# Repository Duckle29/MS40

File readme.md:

View this project on [CADLAB.io](https://cadlab.io/project/2268). 

# MS40

[Interactive BOM](https://duckle29.github.io/MS40/ibom.html)

The project uses Ai03s keyswitch library.
Many thanks to Ai03 for releasing an awesome keyswitch library with an entirely open license.

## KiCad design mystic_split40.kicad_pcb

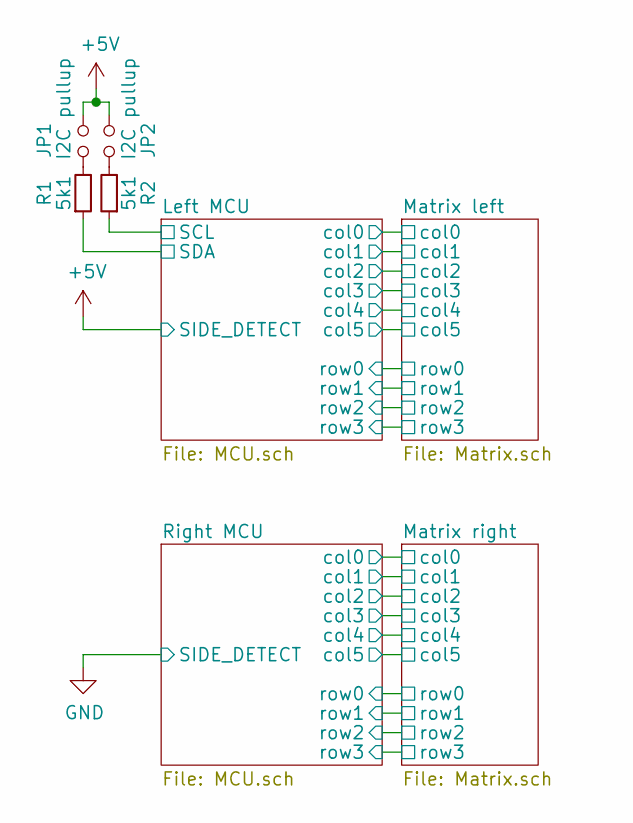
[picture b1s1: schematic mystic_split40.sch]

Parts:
JP1, JP2: I2C pullup; SolderJumper-2_P1.3mm_Open_TrianglePad1.0x1.5mm
R1, R2: 5k1; R_0603_1608Metric_Pad1.05x0.95mm_HandSolder

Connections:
+5V: JP1.1, JP2.1; also elsewhere on the board
/Left MCU/SCL: R2.1; also elsewhere on the board
/Left MCU/SDA: R1.1; also elsewhere on the board
unnamed: JP1.2, R1.2
unnamed: JP2.2, R2.2

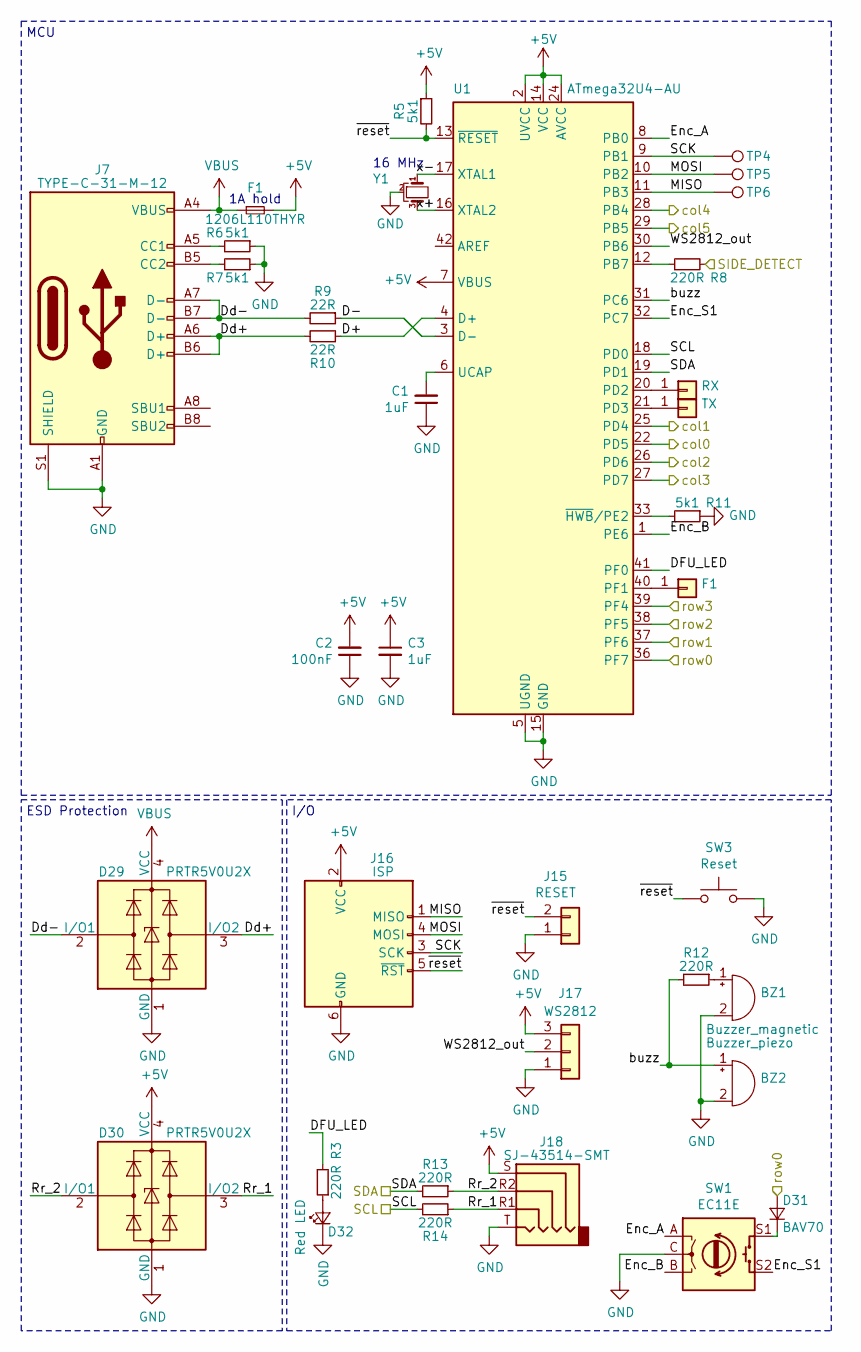
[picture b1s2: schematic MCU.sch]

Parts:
BZ1: Buzzer_magnetic; Buzzer_12x9.5RM7.6
BZ2: Buzzer_piezo; Buzzer_Mallory_AST1109MLTRQ
C1, C3: 1uF; C_0603_1608Metric_Pad1.05x0.95mm_HandSolder
C2: 100nF; C_0603_1608Metric_Pad1.05x0.95mm_HandSolder
D29, D30: PRTR5V0U2X; SOT-143
D31: BAV70; D_SOD-323_HandSoldering
D32: Red LED; LED_0805_2012Metric_Pad1.15x1.40mm_HandSolder
F1: 1206L110THYR; Fuse_1206_3216Metric_Pad1.42x1.75mm_HandSolder
J1: RX; TestPoint_Pad_D1.0mm
J2: TX; TestPoint_Pad_D1.0mm
J6: F1; TestPoint_Pad_D1.0mm
J7: TYPE-C-31-M-12; USB_C_Receptacle_HRO_TYPE-C-31-M-12
J15: RESET; PinHeader_1x02_P2.54mm_Vertical
J16: ISP; Tag-Connect_TC2030-IDC-NL_2x03_P1.27mm_Vertical
J17: WS2812; PinHeader_1x03_P2.54mm_Vertical
J18: SJ-43514-SMT
R3, R8, R12, R13, R14: 220R; R_0603_1608Metric_Pad1.05x0.95mm_HandSolder
R5, R6, R7, R11: 5k1; R_0603_1608Metric_Pad1.05x0.95mm_HandSolder
R9, R10: 22R; R_0603_1608Metric_Pad1.05x0.95mm_HandSolder
SW1: EC11E; RotaryEncoder_Alps_EC11E-Switch_Vertical_H20mm
SW3: Reset; SW_SPST_CK_RS282G05A3
TP4: SCK; TestPoint_Pad_D1.0mm
TP5: MOSI; TestPoint_Pad_D1.0mm
TP6: MISO; TestPoint_Pad_D1.0mm
U1: ATmega32U4-AU; TQFP-44_10x10mm_P0.8mm
Y1: CSTNE16M0VH3L000R0; Resonator_SMD_muRata_CSTxExxV-3Pin_3.0x1.1mm_HandSoldering

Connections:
+5V: C2.2, C3.1, D30.4 (VCC), F1.2, J16.2 (VCC), J17.3, J18.S, R5.1, R8.2, U1.2 (UVCC), U1.7 (VBUS), U1.14 (VCC), U1.24 (AVCC), U1.34 (VCC), U1.44 (AVCC); also elsewhere on the board
/Left MCU/D+: R10.1, U1.4 (D+)
/Left MCU/D-: R9.1, U1.3 (D-)
/Left MCU/DFU_LED: R3.2, U1.41 (PF0)
/Left MCU/Dd+: D29.3 (I/O2), J7.A6 (D+), J7.B6 (D+), R10.2
/Left MCU/Dd-: D29.2 (I/O1), J7.A7 (D-), J7.B7 (D-), R9.2
/Left MCU/Enc_A: SW1.A, U1.8 (PB0)
/Left MCU/Enc_B: SW1.B, U1.1 (PE6)
/Left MCU/Enc_S1: SW1.S2, U1.32 (PC7)
/Left MCU/MISO: J16.1 (MISO), TP6.1, U1.11 (PB3)
/Left MCU/MOSI: J16.4 (MOSI), TP5.1, U1.10 (PB2)
/Left MCU/Rr_1: D30.3 (I/O2), J18.R1, R14.1
/Left MCU/Rr_2: D30.2 (I/O1), J18.R2, R13.1
/Left MCU/SCK: J16.3 (SCK), TP4.1, U1.9 (PB1)
/Left MCU/SCL: R14.2, U1.18 (PD0); also elsewhere on the board
/Left MCU/SDA: R13.2, U1.19 (PD1); also elsewhere on the board
/Left MCU/WS2812_out: J17.2, U1.30 (PB6)
/Left MCU/buzz: BZ2.1 (-), R12.2, U1.31 (PC6)
/Left MCU/col0: U1.22 (PD5); also elsewhere on the board
/Left MCU/col1: U1.25 (PD4); also elsewhere on the board
/Left MCU/col2: U1.26 (PD6); also elsewhere on the board
/Left MCU/col3: U1.27 (PD7); also elsewhere on the board
/Left MCU/col4: U1.28 (PB4); also elsewhere on the board
/Left MCU/col5: U1.29 (PB5); also elsewhere on the board
/Left MCU/row0: D31.2 (A), U1.36 (PF7); also elsewhere on the board
/Left MCU/row1: U1.37 (PF6); also elsewhere on the board
/Left MCU/row2: U1.38 (PF5); also elsewhere on the board
/Left MCU/row3: U1.39 (PF4); also elsewhere on the board
/Left MCU/x+: U1.16 (XTAL2), Y1.3
/Left MCU/x-: U1.17 (XTAL1), Y1.1
/Left MCU/~reset: J15.2, J16.5 (~RST), R5.2, SW3.1, U1.13 (~RESET)
GND: BZ1.2 (+), BZ2.2 (+), C1.1, C2.1, C3.2, D29.1 (GND), D30.1 (GND), D32.1 (K), J7.A1 (GND), J7.A12 (GND), J7.B1 (GND), J7.B12 (GND), J7.S1 (SHIELD), J15.1, J16.6 (GND), J17.1, J18.T, R6.1, R7.1, R11.1, SW1.C, SW1.MP, SW3.2, U1.5 (UGND), U1.15 (GND), U1.23 (GND), U1.35 (GND), U1.43 (GND), Y1.2; also elsewhere on the board
unnamed: BZ1.1 (-), R12.1
unnamed: C1.2, U1.6 (UCAP)
unnamed: D31.1 (K), SW1.S1
unnamed: D32.2 (A), R3.1
unnamed: J1.1, U1.20 (PD2)
unnamed: J2.1, U1.21 (PD3)
unnamed: J6.1, U1.40 (PF1)
unnamed: J7.A5 (CC1), R6.2
unnamed: J7.B5 (CC2), R7.2
unnamed: R8.1, U1.12 (PB7)
unnamed: R11.2, U1.33 (~HWB~/PE2)
VBUS: D29.4 (VCC), F1.1, J7.A4 (VBUS), J7.A9 (VBUS), J7.B4 (VBUS), J7.B9 (VBUS); also elsewhere on the board

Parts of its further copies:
BZ3: Buzzer_magnetic; Buzzer_12x9.5RM7.6
BZ4: Buzzer_piezo; Buzzer_Mallory_AST1109MLTRQ
C4, C6: 1uF; C_0603_1608Metric_Pad1.05x0.95mm_HandSolder
C5: 100nF; C_0603_1608Metric_Pad1.05x0.95mm_HandSolder
D1, D2: PRTR5V0U2X; SOT-143
D27: BAV70; D_SOD-323_HandSoldering
D28: Red LED; LED_0805_2012Metric_Pad1.15x1.40mm_HandSolder
F2: 1206L110THYR; Fuse_1206_3216Metric_Pad1.42x1.75mm_HandSolder
J3: RX; TestPoint_Pad_D1.0mm
J5: TX; TestPoint_Pad_D1.0mm
J9: F1; TestPoint_Pad_D1.0mm
J25: TYPE-C-31-M-12; USB_C_Receptacle_HRO_TYPE-C-31-M-12
J33: RESET; PinHeader_1x02_P2.54mm_Vertical
J34: ISP; Tag-Connect_TC2030-IDC-NL_2x03_P1.27mm_Vertical
J35: WS2812; PinHeader_1x03_P2.54mm_Vertical
J36: SJ-43514-SMT
R4, R18, R22, R23, R24: 220R; R_0603_1608Metric_Pad1.05x0.95mm_HandSolder
R15, R16, R17, R21: 5k1; R_0603_1608Metric_Pad1.05x0.95mm_HandSolder
R19, R20: 22R; R_0603_1608Metric_Pad1.05x0.95mm_HandSolder
SW2: EC11E; RotaryEncoder_Alps_EC11E-Switch_Vertical_H20mm
SW4: Reset; SW_SPST_CK_RS282G05A3
TP1: SCK; TestPoint_Pad_D1.0mm
TP2: MOSI; TestPoint_Pad_D1.0mm
TP3: MISO; TestPoint_Pad_D1.0mm
U2: ATmega32U4-AU; TQFP-44_10x10mm_P0.8mm
Y2: CSTNE16M0VH3L000R0; Resonator_SMD_muRata_CSTxExxV-3Pin_3.0x1.1mm_HandSoldering

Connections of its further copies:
+5V: C5.2, C6.1, D2.4 (VCC), F2.2, J34.2 (VCC), J35.3, J36.S, R15.1, U2.2 (UVCC), U2.7 (VBUS), U2.14 (VCC), U2.24 (AVCC), U2.34 (VCC), U2.44 (AVCC); also elsewhere on the board
/Matrix right/col0: U2.22 (PD5); also elsewhere on the board
/Matrix right/col1: U2.25 (PD4); also elsewhere on the board
/Matrix right/col2: U2.26 (PD6); also elsewhere on the board
/Matrix right/col3: U2.27 (PD7); also elsewhere on the board
/Matrix right/col4: U2.28 (PB4); also elsewhere on the board
/Matrix right/col5: U2.29 (PB5); also elsewhere on the board
/Matrix right/row0: D27.2 (A), U2.36 (PF7); also elsewhere on the board
/Matrix right/row1: U2.37 (PF6); also elsewhere on the board
/Matrix right/row2: U2.38 (PF5); also elsewhere on the board
/Matrix right/row3: U2.39 (PF4); also elsewhere on the board
/Right MCU/D+: R20.1, U2.4 (D+)
/Right MCU/D-: R19.1, U2.3 (D-)
/Right MCU/DFU_LED: R4.2, U2.41 (PF0)
/Right MCU/Dd+: D1.3 (I/O2), J25.A6 (D+), J25.B6 (D+), R20.2
/Right MCU/Dd-: D1.2 (I/O1), J25.A7 (D-), J25.B7 (D-), R19.2
/Right MCU/Enc_A: SW2.A, U2.8 (PB0)
/Right MCU/Enc_B: SW2.B, U2.1 (PE6)
/Right MCU/Enc_S1: SW2.S2, U2.32 (PC7)
/Right MCU/MISO: J34.1 (MISO), TP3.1, U2.11 (PB3)
/Right MCU/MOSI: J34.4 (MOSI), TP2.1, U2.10 (PB2)
/Right MCU/Rr_1: D2.3 (I/O2), J36.R1, R24.1
/Right MCU/Rr_2: D2.2 (I/O1), J36.R2, R23.1
/Right MCU/SCK: J34.3 (SCK), TP1.1, U2.9 (PB1)
/Right MCU/SCL: R24.2, U2.18 (PD0)
/Right MCU/SDA: R23.2, U2.19 (PD1)
/Right MCU/WS2812_out: J35.2, U2.30 (PB6)
/Right MCU/buzz: BZ4.1 (-), R22.2, U2.31 (PC6)
/Right MCU/x+: U2.16 (XTAL2), Y2.3
/Right MCU/x-: U2.17 (XTAL1), Y2.1
/Right MCU/~reset: J33.2, J34.5 (~RST), R15.2, SW4.1, U2.13 (~RESET)
GND: BZ3.2 (+), BZ4.2 (+), C4.1, C5.1, C6.2, D1.1 (GND), D2.1 (GND), D28.1 (K), J25.A1 (GND), J25.A12 (GND), J25.B1 (GND), J25.B12 (GND), J25.S1 (SHIELD), J33.1, J34.6 (GND), J35.1, J36.T, R16.1, R17.1, R18.2, R21.1, SW2.C, SW4.2, U2.5 (UGND), U2.15 (GND), U2.23 (GND), U2.35 (GND), U2.43 (GND), Y2.2; also elsewhere on the board
unnamed: BZ3.1 (-), R22.1
unnamed: C4.2, U2.6 (UCAP)
unnamed: D27.1 (K), SW2.S1
unnamed: D28.2 (A), R4.1
unnamed: J3.1, U2.20 (PD2)
unnamed: J5.1, U2.21 (PD3)
unnamed: J9.1, U2.40 (PF1)
unnamed: J25.A5 (CC1), R16.2
unnamed: J25.B5 (CC2), R17.2
unnamed: R18.1, U2.12 (PB7)
unnamed: R21.2, U2.33 (~HWB~/PE2)
VBUS: D1.4 (VCC), F2.1, J25.A4 (VBUS), J25.A9 (VBUS), J25.B4 (VBUS), J25.B9 (VBUS); also elsewhere on the board

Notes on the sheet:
ESD Protection
MCU
16 MHz
I/O
1A hold

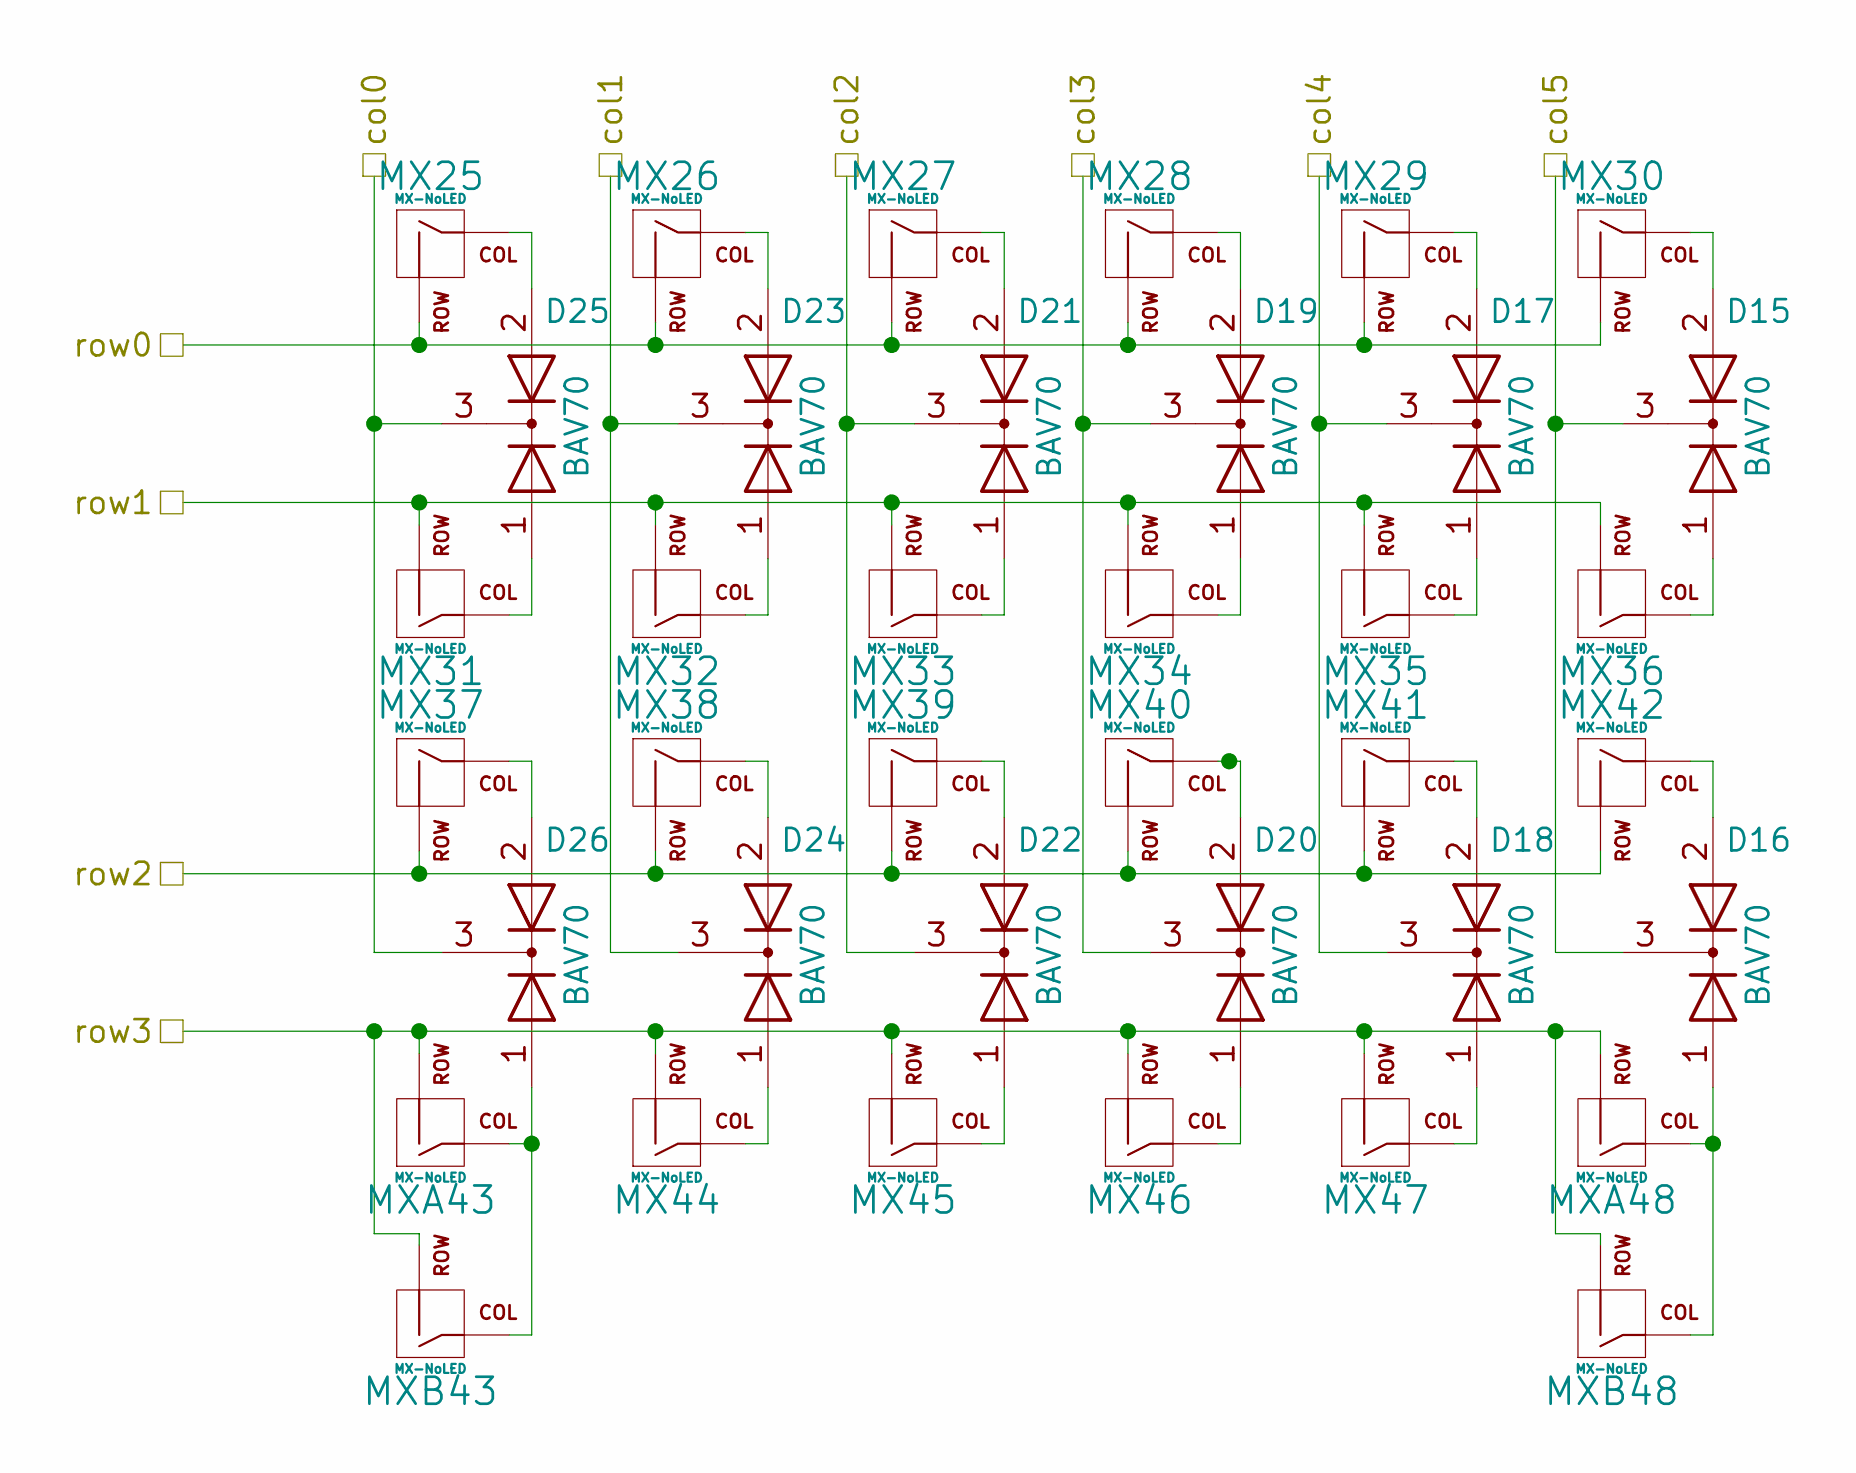
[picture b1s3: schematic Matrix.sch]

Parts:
D3, D4, D5, D6, D7, D8, D9, D10, D11, D12, D13, D14: BAV70; SOT-23_Handsoldering
MX1, MX2, MX3, MX4, MX5, MX6, MX7, MX8, MX9, MX10, MX11, MX12, MX13, MX14, MX15, MX16, MX17, MX18, MX20, MX21, MX22, MX23: MX-NoLED; MXOnly-1U-Hotswap
MXA19, MXA24: MX-NoLED; MXOnly-1U-Hotswap
MXB19, MXB24: MX-NoLED; MXOnly-2U-Hotswap

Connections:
/Left MCU/col0: D13.3 (K), D14.3 (K); also elsewhere on the board
/Left MCU/col1: D11.3 (K), D12.3 (K); also elsewhere on the board
/Left MCU/col2: D9.3 (K), D10.3 (K); also elsewhere on the board
/Left MCU/col3: D7.3 (K), D8.3 (K); also elsewhere on the board
/Left MCU/col4: D5.3 (K), D6.3 (K); also elsewhere on the board
/Left MCU/col5: D3.3 (K), D4.3 (K); also elsewhere on the board
/Left MCU/row0: MX1.2 (ROW), MX2.2 (ROW), MX3.2 (ROW), MX4.2 (ROW), MX5.2 (ROW), MX6.2 (ROW); also elsewhere on the board
/Left MCU/row1: MX7.2 (ROW), MX8.2 (ROW), MX9.2 (ROW), MX10.2 (ROW), MX11.2 (ROW), MX12.2 (ROW); also elsewhere on the board
/Left MCU/row2: MX13.2 (ROW), MX14.2 (ROW), MX15.2 (ROW), MX16.2 (ROW), MX17.2 (ROW), MX18.2 (ROW); also elsewhere on the board
/Left MCU/row3: MX20.2 (ROW), MX21.2 (ROW), MX22.2 (ROW), MX23.2 (ROW), MXA19.2 (ROW), MXA24.2 (ROW), MXB19.2 (ROW), MXB24.2 (ROW); also elsewhere on the board
unnamed: D3.1 (A), MX12.1 (COL)
unnamed: D3.2 (A), MX6.1 (COL)
unnamed: D4.1 (A), MXA24.1 (COL), MXB24.1 (COL)
unnamed: D4.2 (A), MX18.1 (COL)
unnamed: D5.1 (A), MX11.1 (COL)
unnamed: D5.2 (A), MX5.1 (COL)
unnamed: D6.1 (A), MX23.1 (COL)
unnamed: D6.2 (A), MX17.1 (COL)
unnamed: D7.1 (A), MX10.1 (COL)
unnamed: D7.2 (A), MX4.1 (COL)
unnamed: D8.1 (A), MX22.1 (COL)
unnamed: D8.2 (A), MX16.1 (COL)
unnamed: D9.1 (A), MX9.1 (COL)
unnamed: D9.2 (A), MX3.1 (COL)
unnamed: D10.1 (A), MX21.1 (COL)
unnamed: D10.2 (A), MX15.1 (COL)
unnamed: D11.1 (A), MX8.1 (COL)
unnamed: D11.2 (A), MX2.1 (COL)
unnamed: D12.1 (A), MX20.1 (COL)
unnamed: D12.2 (A), MX14.1 (COL)
unnamed: D13.1 (A), MX7.1 (COL)
unnamed: D13.2 (A), MX1.1 (COL)
unnamed: D14.1 (A), MXA19.1 (COL), MXB19.1 (COL)
unnamed: D14.2 (A), MX13.1 (COL)

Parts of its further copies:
D15, D16, D17, D18, D19, D20, D21, D22, D23, D24, D25, D26: BAV70; SOT-23_Handsoldering
MX25, MX26, MX27, MX28, MX29, MX30, MX31, MX32, MX33, MX34, MX35, MX36, MX37, MX38, MX39, MX40, MX41, MX42, MX44, MX45, MX46, MX47: MX-NoLED; MXOnly-1U-Hotswap
MXA43, MXA48: MX-NoLED; MXOnly-1U-Hotswap
MXB43, MXB48: MX-NoLED; MXOnly-2U-Hotswap

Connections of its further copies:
/Matrix right/col0: D25.3 (K), D26.3 (K); also elsewhere on the board
/Matrix right/col1: D23.3 (K), D24.3 (K); also elsewhere on the board
/Matrix right/col2: D21.3 (K), D22.3 (K); also elsewhere on the board
/Matrix right/col3: D19.3 (K), D20.3 (K); also elsewhere on the board
/Matrix right/col4: D17.3 (K), D18.3 (K); also elsewhere on the board
/Matrix right/col5: D15.3 (K), D16.3 (K); also elsewhere on the board
/Matrix right/row0: MX25.2 (ROW), MX26.2 (ROW), MX27.2 (ROW), MX28.2 (ROW), MX29.2 (ROW), MX30.2 (ROW); also elsewhere on the board
/Matrix right/row1: MX31.2 (ROW), MX32.2 (ROW), MX33.2 (ROW), MX34.2 (ROW), MX35.2 (ROW), MX36.2 (ROW); also elsewhere on the board
/Matrix right/row2: MX37.2 (ROW), MX38.2 (ROW), MX39.2 (ROW), MX40.2 (ROW), MX41.2 (ROW), MX42.2 (ROW); also elsewhere on the board
/Matrix right/row3: MX44.2 (ROW), MX45.2 (ROW), MX46.2 (ROW), MX47.2 (ROW), MXA43.2 (ROW), MXA48.2 (ROW), MXB43.2 (ROW), MXB48.2 (ROW); also elsewhere on the board
unnamed: D15.1 (A), MX36.1 (COL)
unnamed: D15.2 (A), MX30.1 (COL)
unnamed: D16.1 (A), MXA48.1 (COL), MXB48.1 (COL)
unnamed: D16.2 (A), MX42.1 (COL)
unnamed: D17.1 (A), MX35.1 (COL)
unnamed: D17.2 (A), MX29.1 (COL)
unnamed: D18.1 (A), MX47.1 (COL)
unnamed: D18.2 (A), MX41.1 (COL)
unnamed: D19.1 (A), MX34.1 (COL)
unnamed: D19.2 (A), MX28.1 (COL)
unnamed: D20.1 (A), MX46.1 (COL)
unnamed: D20.2 (A), MX40.1 (COL)
unnamed: D21.1 (A), MX33.1 (COL)
unnamed: D21.2 (A), MX27.1 (COL)
unnamed: D22.1 (A), MX45.1 (COL)
unnamed: D22.2 (A), MX39.1 (COL)
unnamed: D23.1 (A), MX32.1 (COL)
unnamed: D23.2 (A), MX26.1 (COL)
unnamed: D24.1 (A), MX44.1 (COL)
unnamed: D24.2 (A), MX38.1 (COL)
unnamed: D25.1 (A), MX31.1 (COL)
unnamed: D25.2 (A), MX25.1 (COL)
unnamed: D26.1 (A), MXA43.1 (COL), MXB43.1 (COL)
unnamed: D26.2 (A), MX37.1 (COL)

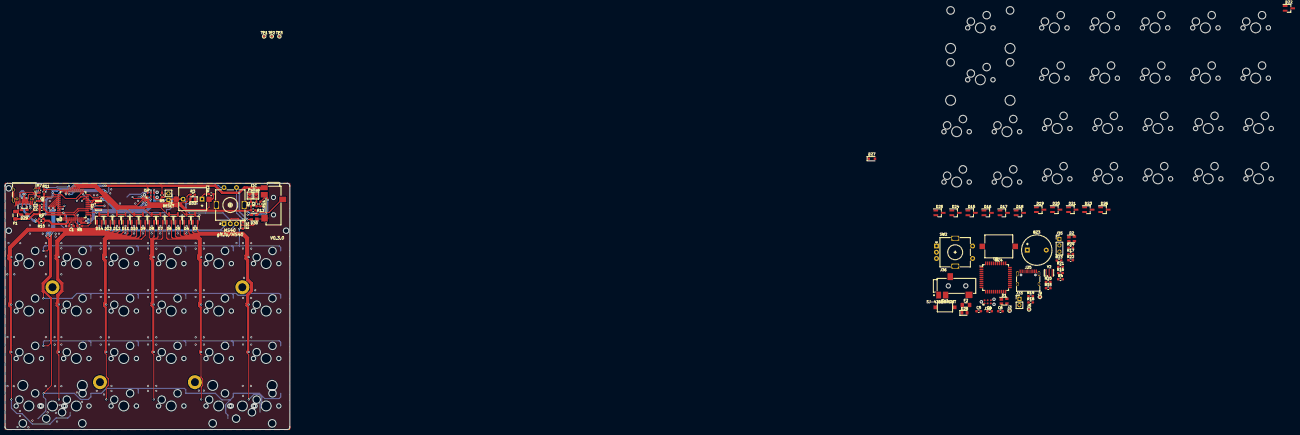
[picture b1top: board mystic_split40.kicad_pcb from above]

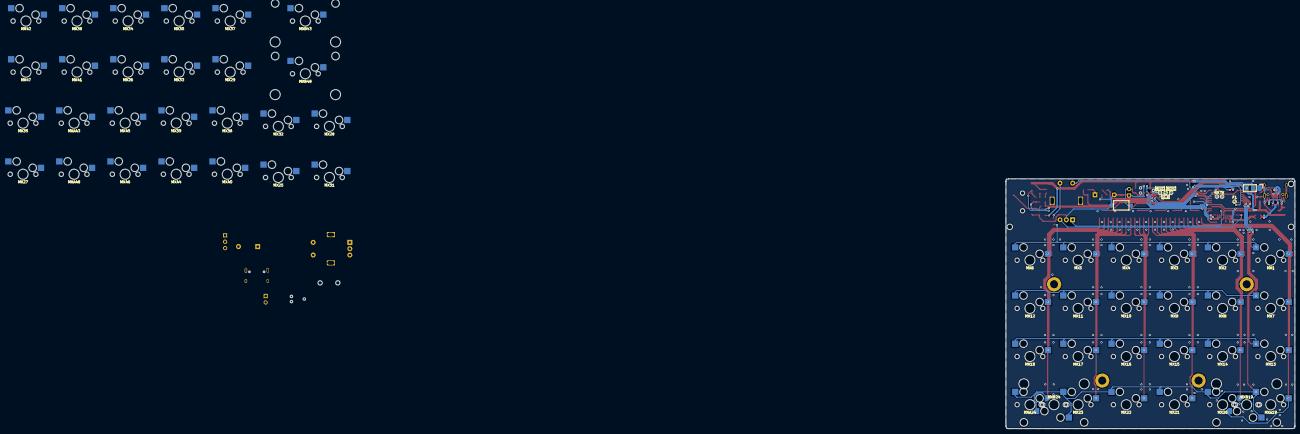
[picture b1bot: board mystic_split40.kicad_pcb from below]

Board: 2 copper layers, 114.3 x 98.8 mm, 152 parts (8 on the bottom side), 135 nets.

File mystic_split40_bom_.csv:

"Id";"Designator";"Package";"Quantity";"Designation";"Supplier and ref";
1;"G***,G***";"kiwi10mm";2;"LOGO";;;
2;"MX44,MX43,MX42,MX41";"MXOnly-2U-Hotswap";4;"MX-NoLED";;;
3;"J5,J2";"TestPoint_Pad_D1.0mm";2;"TX";;;
4;"J3,J1";"TestPoint_Pad_D1.0mm";2;"RX";;;
5;"F2,F1";"Fuse_1206_3216Metric_Pad1.42x1.75mm_HandSolder";2;"?mA fuse";;;
6;"D3,D4,D2,D1";"SOT-143";4;"PRTR5V0U2X";;;
7;"J35,J17";"PinHeader_1x03_P2.54mm_Vertical";2;"WS2812";;;
8;"R15,R17,R16,R21,R5,R11,R7,R6,R2,R1";"R_0603_1608Metric_Pad1.05x0.95mm_HandSolder";10;"5k1";;;
9;"SW2,SW1";"RotaryEncoder_Alps_EC11E-Switch_Vertical_H20mm";2;"EC11E";;;
10;"SW4,SW3";"SW_SPST_CK_RS282G05A3";2;"Reset";;;
11;"D26,D25";"D_SOD-323_HandSoldering";2;"BAV70";;;
12;"MX22,MX36,MX23,MX25,MX37,MX31,MX24,MX27,MX28,MX29,MX30,MX33,MX34,MX32,MX38,MX40,MX26,MX39,MX35,MX21,MX5,MX3,MX16,MX2,MX20,MX19,MX18,MX17,MX15,MX14,MX13,MX12,MX11,MX10,MX9,MX8,MX7,MX6,MX4,MX1";"MXOnly-1U-Hotswap";40;"MX-NoLED";;;
13;"U2,U1";"TQFP-44_10x10mm_P0.8mm";2;"ATmega32U4-AU";;;
14;"J22";"TestPoint_Pad_D1.0mm";1;"AREF";;;
15;"J36,J18";"SJ-43514-SMT";2;"SJ-43514-SMT";;;
16;"BZ3,BZ1";"Buzzer_12x9.5RM7.6";2;"Buzzer_magnetic";;;
17;"R4,R24,R23,R22,R18,R3,R14,R13,R12,R8";"R_0603_1608Metric_Pad1.05x0.95mm_HandSolder";10;"220R";;;
18;"D28,D27";"LED_0805_2012Metric_Pad1.15x1.40mm_HandSolder";2;"Red LED";;;
19;"REF**,REF**,REF**,REF**,REF**,REF**";"MountingHole_2.2mm_M2_DIN965";6;"MountingHole_2.2mm_M2_DIN965";;;
20;"REF**,REF**,REF**,REF**,REF**,REF**,REF**,REF**";"MountingHole_3.2mm_M3_DIN965_Pad";8;"MountingHole_3.2mm_M3_DIN965_Pad";;;
21;"C5,C2";"C_0603_1608Metric_Pad1.05x0.95mm_HandSolder";2;"100nF";;;
22;"C4,C6,C3,C1";"C_0603_1608Metric_Pad1.05x0.95mm_HandSolder";4;"1uF";;;
23;"D15,D23,D21,D19,D22,D18,D20,D17,D24,D16,D6,D8,D10,D12,D14,D5,D7,D9,D11,D13";"SOT-23_Handsoldering";20;"BAV70";;;
24;"BZ4,BZ2";"Buzzer_Mallory_AST1109MLTRQ";2;"Buzzer_piezo";;;
25;"Y2,Y1";"Resonator_SMD_muRata_CSTxExxV-3Pin_3.0x1.1mm_HandSoldering";2;"CSTNE16M0VH3L000R0";;;
26;"R20,R19,R10,R9";"R_0603_1608Metric_Pad1.05x0.95mm_HandSolder";4;"22R";;;
27;"J25,J7";"USB_C_Receptacle_HRO_TYPE-C-31-M-12";2;"TYPE-C-31-M-12";;;
28;"J33,J15";"PinHeader_1x02_P2.54mm_Vertical";2;"RESET";;;
29;"J34,J16";"Tag-Connect_TC2030-IDC-NL_2x03_P1.27mm_Vertical";2;"ISP";;;
30;"JP2,JP1";"SolderJumper-2_P1.3mm_Open_TrianglePad1.0x1.5mm";2;"I2C pullup";;;

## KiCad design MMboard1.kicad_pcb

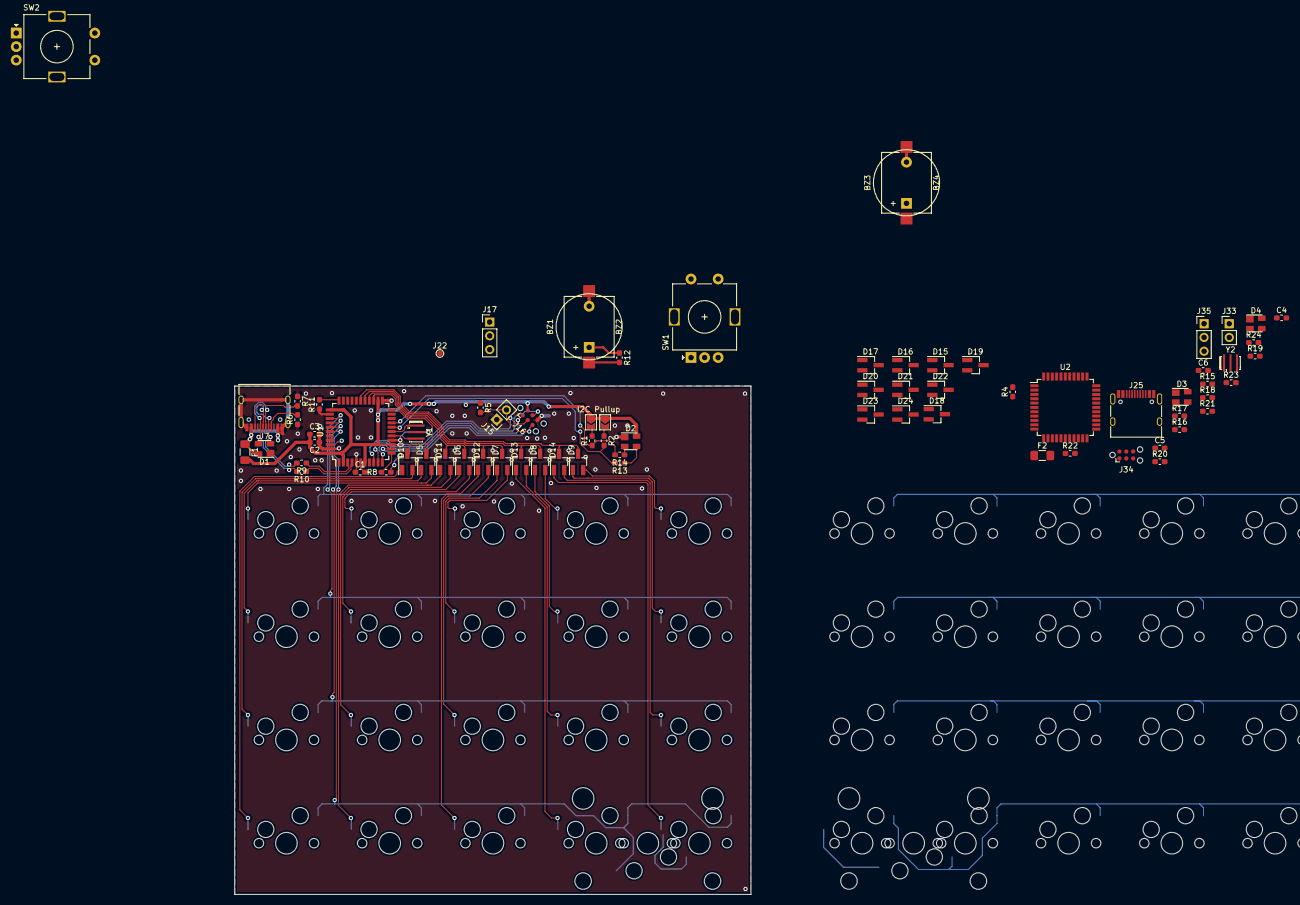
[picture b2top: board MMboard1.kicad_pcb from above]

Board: 2 copper layers, 95.2 x 93.8 mm, 119 parts (1 on the bottom side), 107 nets.

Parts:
BZ1, BZ3: Buzzer_magnetic; Buzzer_12x9.5RM7.6
BZ2, BZ4: Buzzer_piezo; Buzzer_Mallory_AST1109MLTRQ
C1, C3, C4, C6: 1uF; C_0603_1608Metric_Pad1.05x0.95mm_HandSolder
C2, C5: 100nF; C_0603_1608Metric_Pad1.05x0.95mm_HandSolder
D1, D2, D3, D4: PRTR5V0U2X; SOT-143
D5, D6, D7, D8, D9, D10, D11, D12, D13, D14, D15, D16, D17, D18, D19, D20, D21, D22, D23, D24: BAV70; SOT-23_Handsoldering
F1, F2: ?mA fuse; Fuse_1206_3216Metric_Pad1.42x1.75mm_HandSolder
J4, J22: AREF; TestPoint_Pad_D1.0mm
J7, J25: TYPE-C-31-M-12; USB_C_Receptacle_HRO_TYPE-C-31-M-12
J15, J33: RESET; PinHeader_1x02_P2.54mm_Vertical
J16, J34: AVR-ISP-6; Tag-Connect_TC2030-IDC-NL_2x03_P1.27mm_Vertical
J17, J35: WS2812; PinHeader_1x03_P2.54mm_Vertical
JP1, JP2: I2C pullup; SolderJumper-2_P1.3mm_Open_TrianglePad1.0x1.5mm
MX1, MX2, MX3, MX4, MX5, MX6, MX7, MX8, MX9, MX10, MX11, MX12, MX13, MX14, MX15, MX16, MX17, MX18, MX19, MX20, MX21, MX22, MX23, MX24, MX25, MX26, MX27, MX28, MX29, MX30, MX31, MX32, MX33, MX34, MX35, MX36, MX37, MX38, MX39, MX40: MX-NoLED; MXOnly-1U-Hotswap
MX41, MX42: MX-NoLED; MXOnly-2U-Hotswap
R1, R2, R4, R5, R6, R7, R11, R15, R16, R17, R21: 5k1; R_0603_1608Metric_Pad1.05x0.95mm_HandSolder
R8, R12, R13, R14, R18, R22, R23, R24: 220R; R_0603_1608Metric_Pad1.05x0.95mm_HandSolder
R9, R10, R19, R20: 22R; R_0603_1608Metric_Pad1.05x0.95mm_HandSolder
SW1, SW2: EC11E; RotaryEncoder_Alps_EC11E-Switch_Vertical_H20mm
U1, U2: ATmega32U4-AU; TQFP-44_10x10mm_P0.8mm
Y1, Y2: CSTNE16M0VH3L000R0; Resonator_SMD_muRata_CSTxExxV-3Pin_3.0x1.1mm_HandSoldering

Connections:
+5V: C2.2, C3.1, C5.2, C6.1, D2.4, D4.4, F1.2, F2.2, J16.2, J17.3, J34.2, J35.3, JP1.1, JP2.1, R5.1, R8.2, R15.1, U1.2, U1.7, U1.14, U1.24, U1.34, U1.44, U2.2, U2.7, U2.14, U2.24, U2.34, U2.44
/Left MCU/D+: R10.1, U1.4
/Left MCU/D-: R9.1, U1.3
/Left MCU/Dd+: D1.3, J7.A6, J7.B6, R10.2
/Left MCU/Dd-: D1.2, J7.A7, J7.B7, R9.2
/Left MCU/MISO: J16.1, U1.11
/Left MCU/MOSI: J16.4, U1.10
/Left MCU/Rr_1: D2.2, R14.1
/Left MCU/Rr_2: D2.3, R13.1
/Left MCU/SCK: J16.3, U1.9
/Left MCU/SCL: R2.1, R13.2, U1.18
/Left MCU/SDA: R1.1, R14.2, U1.19
/Left MCU/buzz: BZ2.1, R12.2
/Left MCU/col0: D5.3, D10.3, U1.22
/Left MCU/col1: D6.3, D11.3, U1.25
/Left MCU/col2: D7.3, D12.3, U1.26
/Left MCU/col3: D8.3, D13.3, U1.27
/Left MCU/col4: D9.3, D14.3, U1.28
/Left MCU/row0: MX1.2, MX2.2, MX3.2, MX4.2, MX5.2, U1.36
/Left MCU/row1: MX6.2, MX7.2, MX8.2, MX9.2, MX10.2, U1.37
/Left MCU/row2: MX11.2, MX12.2, MX13.2, MX14.2, MX15.2, U1.38
/Left MCU/row3: MX16.2, MX17.2, MX18.2, MX19.2, MX20.2, MX41.2, U1.39
/Left MCU/~reset: J15.2, J16.5, R5.2, U1.13
/Matrix right/col0: D15.3, D20.3, U2.22
/Matrix right/col1: D16.3, D21.3, U2.25
/Matrix right/col2: D17.3, D22.3, U2.26
/Matrix right/col3: D18.3, D23.3, U2.27
/Matrix right/col4: D19.3, D24.3, U2.28
/Matrix right/row0: MX21.2, MX22.2, MX23.2, MX24.2, MX25.2, U2.36
/Matrix right/row1: MX26.2, MX27.2, MX28.2, MX29.2, MX30.2, U2.37
/Matrix right/row2: MX31.2, MX32.2, MX33.2, MX34.2, MX35.2, U2.38
/Matrix right/row3: MX36.2, MX37.2, MX38.2, MX39.2, MX40.2, MX42.2, U2.39
/Right MCU/D+: R20.1, U2.4
/Right MCU/D-: R19.1, U2.3
/Right MCU/Dd+: D3.3, J25.A6, J25.B6, R20.2
/Right MCU/Dd-: D3.2, J25.A7, J25.B7, R19.2
/Right MCU/MISO: J34.1, U2.11
/Right MCU/MOSI: J34.4, U2.10
/Right MCU/Rr_1: D4.2, R24.1
/Right MCU/Rr_2: D4.3, R23.1
/Right MCU/SCK: J34.3, U2.9
/Right MCU/SCL: R23.2, U2.18
/Right MCU/SDA: R24.2, U2.19
/Right MCU/buzz: BZ4.1, R22.2
/Right MCU/~reset: J33.2, J34.5, R15.2, U2.13
GND: BZ1.2, BZ2.2, BZ3.2, BZ4.2, C1.1, C2.1, C3.2, C4.1, C5.1, C6.2, D1.1, D2.1, D3.1, D4.1, J7.A1, J7.A12, J7.B1, J7.B12, J7.S1, J15.1, J16.6, J17.1, J25.A1, J25.A12, J25.B1, J25.B12, J25.S1, J33.1, J34.6, J35.1, R4.1, R6.1, R7.1, R11.1, R16.1, R17.1, R18.2, R21.1, SW1.C, SW1.S2, SW2.C, SW2.S2, U1.5, U1.15, U1.23, U1.35, U1.43, U2.5, U2.15, U2.23, U2.35, U2.43, Y1.2, Y2.2
unnamed: BZ1.1, R12.1
unnamed: BZ3.1, R22.1
unnamed: C1.2, U1.6
unnamed: C4.2, U2.6
unnamed: D5.1, MX6.1
unnamed: D5.2, MX1.1
unnamed: D6.1, MX7.1
unnamed: D6.2, MX2.1
unnamed: D7.1, MX8.1
unnamed: D7.2, MX3.1
unnamed: D8.1, MX9.1
unnamed: D8.2, MX4.1
unnamed: D9.1, MX10.1
unnamed: D9.2, MX5.1
unnamed: D10.1, MX16.1
unnamed: D10.2, MX11.1
unnamed: D11.1, MX17.1
unnamed: D11.2, MX12.1
unnamed: D12.1, MX18.1
unnamed: D12.2, MX13.1
unnamed: D13.1, MX19.1
unnamed: D13.2, MX14.1
unnamed: D14.1, MX20.1, MX41.1
unnamed: D14.2, MX15.1
unnamed: D15.1, MX26.1
unnamed: D15.2, MX21.1
unnamed: D16.1, MX27.1
unnamed: D16.2, MX22.1
unnamed: D17.1, MX28.1
unnamed: D17.2, MX23.1
unnamed: D18.1, MX29.1
unnamed: D18.2, MX24.1
unnamed: D19.1, MX30.1
unnamed: D19.2, MX25.1
unnamed: D20.1, MX36.1
unnamed: D20.2, MX31.1
unnamed: D21.1, MX37.1
unnamed: D21.2, MX32.1
unnamed: D22.1, MX38.1
unnamed: D22.2, MX33.1
unnamed: D23.1, MX39.1
unnamed: D23.2, MX34.1
unnamed: D24.1, MX40.1, MX42.1
unnamed: D24.2, MX35.1
unnamed: J4.1, U1.42
unnamed: J7.A5, R6.2
unnamed: J7.B5, R7.2
unnamed: J22.1, U2.42
unnamed: J25.A5, R16.2
unnamed: J25.B5, R17.2
unnamed: JP1.2, R1.2
unnamed: JP2.2, R2.2
unnamed: R8.1, U1.12
unnamed: R11.2, U1.33
unnamed: R18.1, U2.12
unnamed: R21.2, U2.33
unnamed: U1.16, Y1.3
unnamed: U1.17, Y1.1
unnamed: U2.16, Y2.3
unnamed: U2.17, Y2.1
VBUS: D1.4, D3.4, F1.1, F2.1, J7.A4, J7.A9, J7.B4, J7.B9, J25.A4, J25.A9, J25.B4, J25.B9

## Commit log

2019-11-04 Updated symbol library names
2019-11-04 Backlink to CADLAB.io has been added.
2019-11-04 Added CUI connector lib
2019-11-04 Renamed board
2019-11-04 Added 3D models, prettied up silk
2019-11-05 Copied left half layout to right components
2019-11-05 Finished right-side, added BOM
2019-11-05 Added CSV BOM
2019-11-06 Started work on hosting ibom on gh-pages
2019-11-06 Added very simple index
2019-11-06 Fixed up silkscreen
2019-11-06 Moved WS2812 pads and added pinout
2019-11-06 Added kicad renders
2019-11-06 Further silk cleanup
2019-11-07 Added 3D model
2019-11-08 Added qmk hardware lib
2019-11-08 Bump pillow from 4.3.0 to 6.2.0 in /lib/qmk_hardware/tools
    Bumps [pillow](https://github.com/python-pillow/Pillow) from 4.3.0 to 6.2.0.
    - [Release notes](https://github.com/python-pillow/Pillow/releases)
    - [Changelog](https://github.com/python-pillow/Pillow/blob/master/CHANGES.rst)
    - [Commits](https://github.com/python-pillow/Pillow/compare/4.3.0...6.2.0)
2019-11-10 Connected USB shield via RC filter, updated renders
2019-11-10 Saved pcbnew
2019-11-11 Swapped SDA and SCL pins on TRRS jack
2019-11-11 Changed right USB peg holes to solid pour connection
2019-11-11 Improved ground routing from ISP header
2019-11-12 regenerated gerbers
2020-01-19 Started work on adding extra col
2020-01-19 Changed version silk
2020-03-11 Fixed iBOM link
2021-03-19 Bump pillow from 4.3.0 to 8.1.1 in /lib/qmk_hardware/tools
    Bumps [pillow](https://github.com/python-pillow/Pillow) from 4.3.0 to 8.1.1.
    - [Release notes](https://github.com/python-pillow/Pillow/releases)
    - [Changelog](https://github.com/python-pillow/Pillow/blob/master/CHANGES.rst)
    - [Commits](https://github.com/python-pillow/Pillow/compare/4.3.0...8.1.1)
2021-06-08 Bump pillow from 4.3.0 to 8.2.0 in /lib/qmk_hardware/tools
    Bumps [pillow](https://github.com/python-pillow/Pillow) from 4.3.0 to 8.2.0.
    - [Release notes](https://github.com/python-pillow/Pillow/releases)
    - [Changelog](https://github.com/python-pillow/Pillow/blob/master/CHANGES.rst)
    - [Commits](https://github.com/python-pillow/Pillow/compare/4.3.0...8.2.0)
    ---
    updated-dependencies:
2021-09-08 Bump pillow from 4.3.0 to 8.3.2 in /lib/qmk_hardware/tools
    Bumps [pillow](https://github.com/python-pillow/Pillow) from 4.3.0 to 8.3.2.
    - [Release notes](https://github.com/python-pillow/Pillow/releases)
    - [Changelog](https://github.com/python-pillow/Pillow/blob/master/CHANGES.rst)
    - [Commits](https://github.com/python-pillow/Pillow/compare/4.3.0...8.3.2)
    ---
    updated-dependencies:
2022-01-13 Bump pillow from 4.3.0 to 9.0.0 in /lib/qmk_hardware/tools
    Bumps [pillow](https://github.com/python-pillow/Pillow) from 4.3.0 to 9.0.0.
    - [Release notes](https://github.com/python-pillow/Pillow/releases)
    - [Changelog](https://github.com/python-pillow/Pillow/blob/main/CHANGES.rst)
    - [Commits](https://github.com/python-pillow/Pillow/compare/4.3.0...9.0.0)
    ---
    updated-dependencies:
2022-03-12 Bump pillow from 4.3.0 to 9.0.1 in /lib/qmk_hardware/tools
    Bumps [pillow](https://github.com/python-pillow/Pillow) from 4.3.0 to 9.0.1.
    - [Release notes](https://github.com/python-pillow/Pillow/releases)
    - [Changelog](https://github.com/python-pillow/Pillow/blob/main/CHANGES.rst)
    - [Commits](https://github.com/python-pillow/Pillow/compare/4.3.0...9.0.1)
    ---
    updated-dependencies:
2022-06-21 Bump numpy from 1.13.3 to 1.22.0 in /lib/qmk_hardware/tools
    Bumps [numpy](https://github.com/numpy/numpy) from 1.13.3 to 1.22.0.
    - [Release notes](https://github.com/numpy/numpy/releases)
    - [Changelog](https://github.com/numpy/numpy/blob/main/doc/HOWTO_RELEASE.rst)
    - [Commits](https://github.com/numpy/numpy/compare/v1.13.3...v1.22.0)
    ---
    updated-dependencies:
2022-11-22 Bump pillow from 4.3.0 to 9.3.0 in /lib/qmk_hardware/tools
    Bumps [pillow](https://github.com/python-pillow/Pillow) from 4.3.0 to 9.3.0.
    - [Release notes](https://github.com/python-pillow/Pillow/releases)
    - [Changelog](https://github.com/python-pillow/Pillow/blob/main/CHANGES.rst)
    - [Commits](https://github.com/python-pillow/Pillow/compare/4.3.0...9.3.0)
    ---
    updated-dependencies:
2023-10-03 Bump pillow from 4.3.0 to 10.0.1 in /lib/qmk_hardware/tools
    Bumps [pillow](https://github.com/python-pillow/Pillow) from 4.3.0 to 10.0.1.
    - [Release notes](https://github.com/python-pillow/Pillow/releases)
    - [Changelog](https://github.com/python-pillow/Pillow/blob/main/CHANGES.rst)
    - [Commits](https://github.com/python-pillow/Pillow/compare/4.3.0...10.0.1)
    ---
    updated-dependencies:
